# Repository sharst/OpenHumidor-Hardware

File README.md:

# OpenHumidor-Hardware
KiCad files of the OpenHumidor sensor PCB.
Files for 3D-printed humidifier parts, enclosures of the sensor board, etc.

Copyright 2016 Simon Harst

These files are licenced under the GPL v3 Licence, see LICENCE file.

I have included former versions of the PCB in separate folders. 

Versions 2 and 3 were created using the free version of EAGLE. Since version 4, boards are created with KICAD. 

## Ordering PCBs
The current version of the board is v0.6-mega. I'm currently testing all functions but minor bugs might still occur. If you're interested in trying out this project, you should consider contacting me.

So far, I have only ordered with two companies: 
* [PCB-pool](www.pcb-pool.de), located in Germany, the cheapest option takes about 2 weeks incl. shipping, you can directly upload the .kicad_pcb-file. 
* [Seeed Studio](http://www.seeedstudio.com/service/index.php?r=pcb), located in China and a lot cheaper (~14Euros for 10 pcbs). Takes about a month including shipping. You need to upload the .zip-file that's included in the gerber/ folder.

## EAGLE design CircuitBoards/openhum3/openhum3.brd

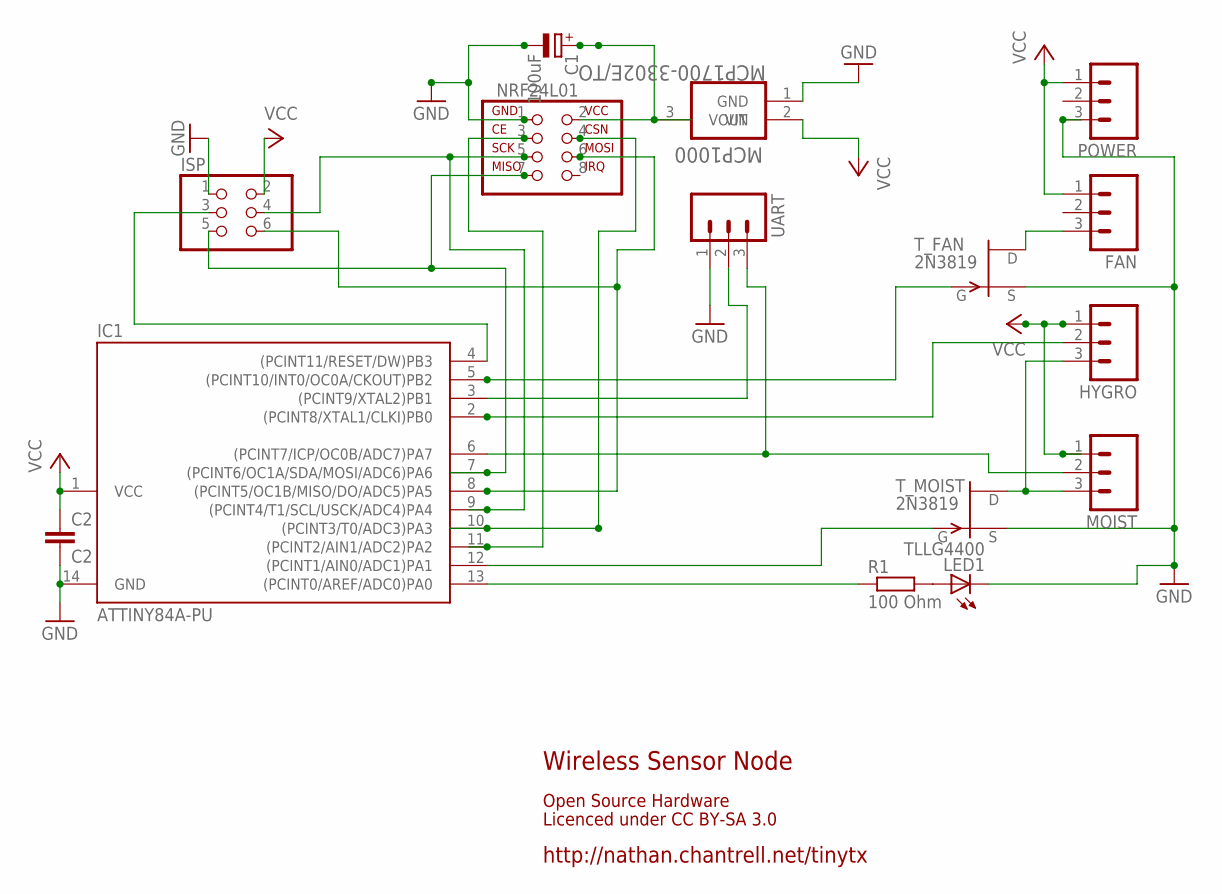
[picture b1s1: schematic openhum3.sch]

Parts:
C1: 100uF; E2,5-6
C2: C2; C025-025X050
FAN: M03JST-PTH; JST-3-PTH
HYGRO: M03JST-PTH; JST-3-PTH
IC1: ATTINY84A-PU; DIL14
ISP: PINHD-2X3; 2X03
LED1: TLLG4400; LED3MM
MCP1000: MCP1700-3302E/TO; TO127P254X495-3
MOIST: M03JST-PTH; JST-3-PTH
NRF24L01: NRF24L01+
POWER: M03JST-PTH; JST-3-PTH
R1: 100 Ohm; 0204/5
T_FAN: 2N3819; TO92
T_MOIST: 2N3819; TO92
UART: M03JST-PTH; JST-3-PTH

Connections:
GND: C1.-, C2.2, IC1.14 (GND), ISP.1, LED1.K (C), MCP1000.1 (GND), NRF24L01.1, POWER.3, T_FAN.3 (S), T_MOIST.3 (S), UART.1
unnamed: IC1.11 ((PCINT2/AIN1/ADC2)PA2), NRF24L01.3
unnamed: IC1.10 ((PCINT3/T0/ADC3)PA3), NRF24L01.4
unnamed: IC1.9 ((PCINT4/T1/SCL/USCK/ADC4)PA4), ISP.4, NRF24L01.5
unnamed: IC1.7 ((PCINT6/OC1A/SDA/MOSI/ADC6)PA6), ISP.5, NRF24L01.7
unnamed: FAN.3, T_FAN.1 (D)
unnamed: IC1.5 ((PCINT10/INT0/OC0A/CKOUT)PB2), T_FAN.2 (G)
unnamed: IC1.3 ((PCINT9/XTAL2)PB1), UART.2
unnamed: C1.+, MCP1000.3 (VOUT), NRF24L01.2
unnamed: IC1.12 ((PCINT1/AIN0/ADC1)PA1), T_MOIST.2 (G)
unnamed: IC1.13 ((PCINT0/AREF/ADC0)PA0), R1.1
unnamed: IC1.8 ((PCINT5/OC1B/MISO/DO/ADC5)PA5), ISP.6, NRF24L01.6
unnamed: HYGRO.2, IC1.2 ((PCINT8/XTAL1/CLKI)PB0)
unnamed: IC1.4 ((PCINT11/RESET/DW)PB3), ISP.3
unnamed: HYGRO.3, MOIST.3, T_MOIST.1 (D)
unnamed: IC1.6 ((PCINT7/ICP/OC0B/ADC7)PA7), MOIST.2, UART.3
unnamed: LED1.A, R1.2
VCC: C2.1, FAN.1, HYGRO.1, IC1.1 (VCC), ISP.2, MCP1000.2 (VIN), MOIST.1, POWER.1

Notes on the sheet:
http://nathan.chantrell.net/tinytx
Wireless Sensor Node
Licenced under CC BY-SA 3.0
Open Source Hardware

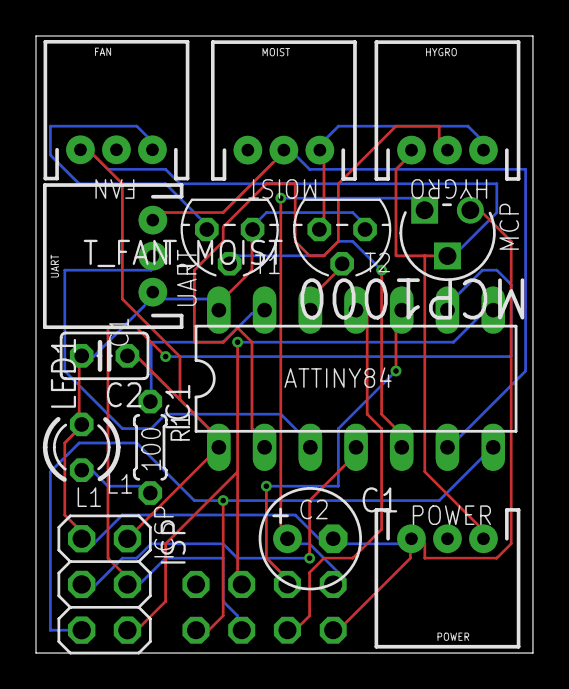
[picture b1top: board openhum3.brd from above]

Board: 2 copper layers, 27.6 x 34.3 mm, 15 parts (1 on the bottom side), 18 nets.

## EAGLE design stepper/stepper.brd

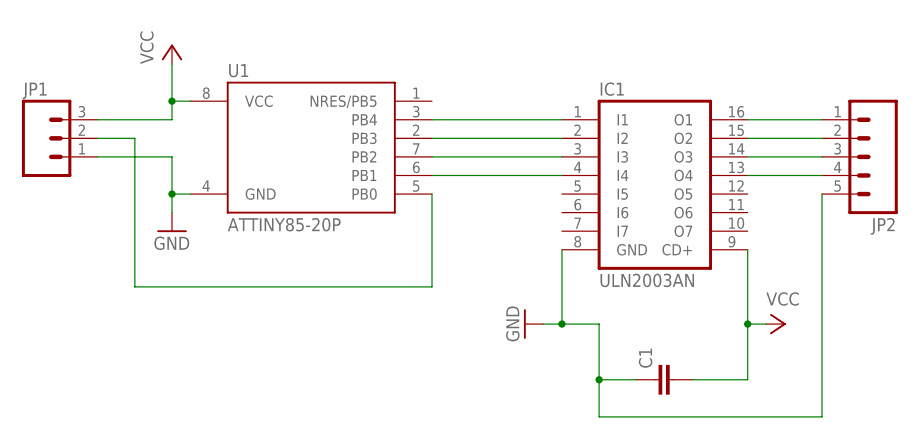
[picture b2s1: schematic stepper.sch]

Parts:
C1: C-EU025-025X050; C025-025X050
IC1: ULN2003AN; DIL16
JP1: M03JST-PTH; JST-3-PTH
JP2: M05PTH_LONGPADS; 1X05_LONGPADS
U1: ATTINY85-20P; PDIP08_300MIL

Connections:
GND: C1.1, IC1.8 (GND), JP1.1, JP2.5, U1.4 (GND)
unnamed: IC1.1 (I1), U1.3 (PB4)
unnamed: IC1.2 (I2), U1.2 (PB3)
unnamed: IC1.3 (I3), U1.7 (PB2)
unnamed: IC1.4 (I4), U1.6 (PB1)
unnamed: JP1.2, U1.5 (PB0)
unnamed: IC1.16 (O1), JP2.1
unnamed: IC1.15 (O2), JP2.2
unnamed: IC1.14 (O3), JP2.3
unnamed: IC1.13 (O4), JP2.4
VCC: C1.2, IC1.9 (CD+), JP1.3, U1.8 (VCC)

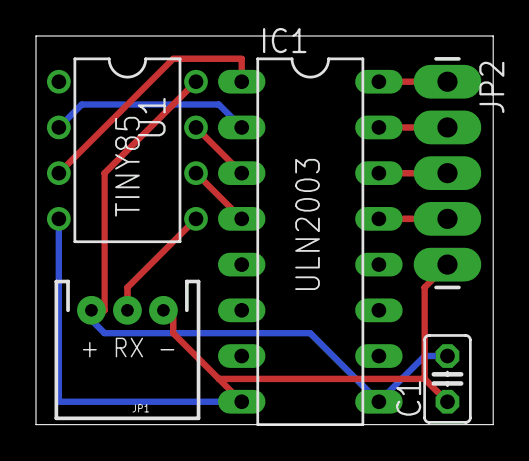
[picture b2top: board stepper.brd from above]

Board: 2 copper layers, 25.4 x 21.6 mm, 5 parts (0 on the bottom side), 11 nets.

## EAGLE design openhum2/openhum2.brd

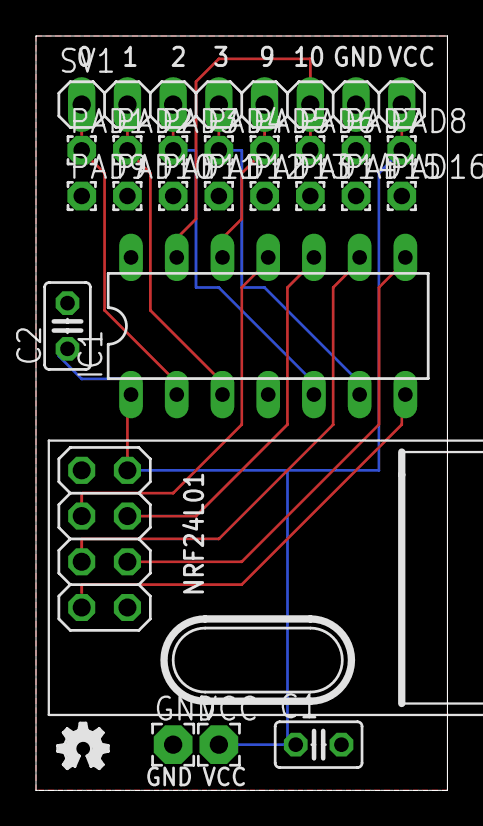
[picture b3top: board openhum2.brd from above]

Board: 2 copper layers, 22.9 x 41.9 mm, 24 parts (0 on the bottom side), 13 nets.

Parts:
C1: C1; C025-025X050
C2: C2; C025-025X050
GND: 2,15/1,0
IC1: ATTINY84A-PU; DIL14
NRF24L01: NRF24L01+
PAD1, PAD2, PAD3, PAD4, PAD5, PAD6, PAD7, PAD8, PAD9, PAD10, PAD11, PAD12, PAD13, PAD14, PAD15, PAD16: 1,6/0,9
SV1: 1X08
U$2: OSHW_FILLX100_NOTEXT
VCC: 2,15/1,0

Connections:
GND: C1.2, C2.2, GND.1, IC1.14, NRF24L01.1, PAD7.1, SV1.7
unnamed: IC1.11, NRF24L01.3
unnamed: IC1.10, NRF24L01.4
unnamed: IC1.9, NRF24L01.5
unnamed: IC1.7, NRF24L01.7
unnamed: IC1.5, PAD3.1, SV1.3
unnamed: IC1.3, PAD2.1, SV1.2
unnamed: IC1.13, PAD6.1, SV1.6
unnamed: IC1.12, PAD5.1, SV1.5
unnamed: IC1.8, NRF24L01.6
unnamed: IC1.2, PAD1.1, SV1.1
unnamed: IC1.6, PAD4.1, SV1.4
VCC: C1.1, C2.1, IC1.1, NRF24L01.2, PAD8.1, SV1.8, VCC.1

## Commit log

2016-01-14 First commit of OpenHumidor PCB project
2016-01-16 Added BOM for OpenHumidor v4
2016-03-12 File version updates to board v5. Added board for new arduino nano base station
2016-06-01 First production version of display PCB
2016-08-13 Newest version of openhumidor board: v0.6
2016-08-13 Add production drawings of PCB
2016-08-13 First STL version of humidifiers.
2016-08-13 Reorganized repository; added sketchup and STL files + lots of documentation
2016-08-22 Added gaps for printing, added battery pack

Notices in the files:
parts and their libraries:
SparkFun-Connectors: Licensing: Creative Commons ShareAlike 4.0 International - https://creativecommons.org/licenses/by-sa/4.0
